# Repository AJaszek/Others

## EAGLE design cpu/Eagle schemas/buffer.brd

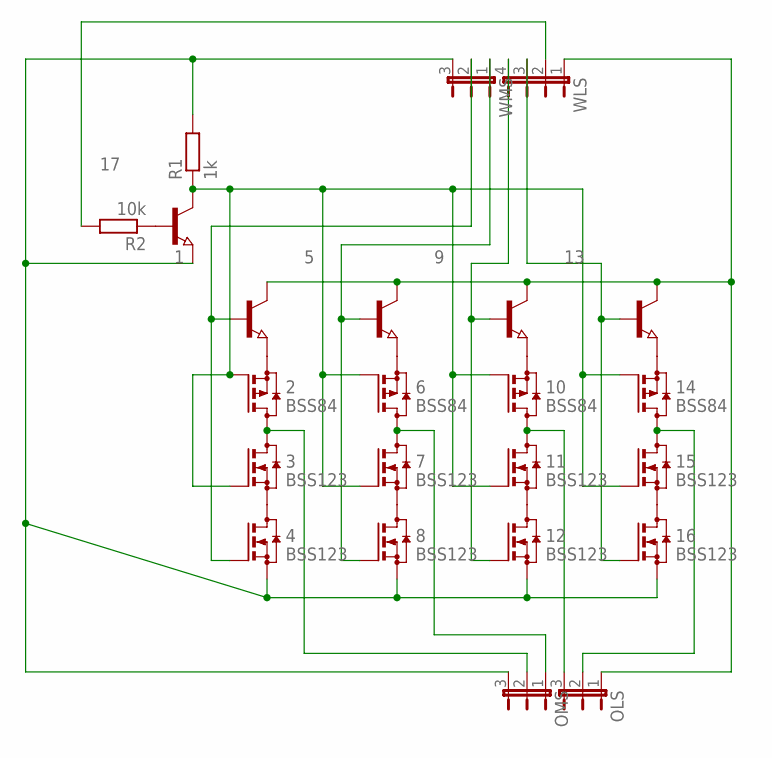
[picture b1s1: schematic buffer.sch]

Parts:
1, 5, 9, 13, 17: NPN-TRANSISTOR_SOT23; SOT23
2, 6, 10, 14: BSS84; SOT23
3, 4, 7, 8, 11, 12, 15, 16: BSS123; SOT23
OLS: JP2E; JP2
OMS: JP2E; JP2
R1: 1k; R1206
R2: 10k; R1206
WLS: JP4E; JP4
WMS: JP2E; JP2

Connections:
unnamed: 13.2 (E), 14.2 (S)
unnamed: 14.3 (D), 15.3 (D), OLS.2
unnamed: 15.2 (S), 16.3 (D)
unnamed: 1.3 (C), 5.3 (C), 9.3 (C), 13.3 (C), OLS.1, WLS.1
unnamed: 13.1 (B), 16.1 (G), WLS.3
unnamed: 4.2 (S), 8.2 (S), 12.2 (S), 16.2 (S), 17.2 (E), OMS.3, R1.2, WMS.3
unnamed: 9.2 (E), 10.2 (S)
unnamed: 10.3 (D), 11.3 (D), OLS.3
unnamed: 11.2 (S), 12.3 (D)
unnamed: 9.1 (B), 12.1 (G), WLS.4
unnamed: 5.2 (E), 6.2 (S)
unnamed: 6.3 (D), 7.3 (D), OMS.1
unnamed: 7.2 (S), 8.3 (D)
unnamed: 5.1 (B), 8.1 (G), WMS.1
unnamed: 1.2 (E), 2.2 (S)
unnamed: 2.3 (D), 3.3 (D), OMS.2
unnamed: 3.2 (S), 4.3 (D)
unnamed: 1.1 (B), 4.1 (G), WMS.2
unnamed: 2.1 (G), 3.1 (G), 6.1 (G), 7.1 (G), 10.1 (G), 11.1 (G), 14.1 (G), 15.1 (G), 17.3 (C), R1.1
unnamed: 17.1 (B), R2.1
unnamed: R2.2, WLS.2

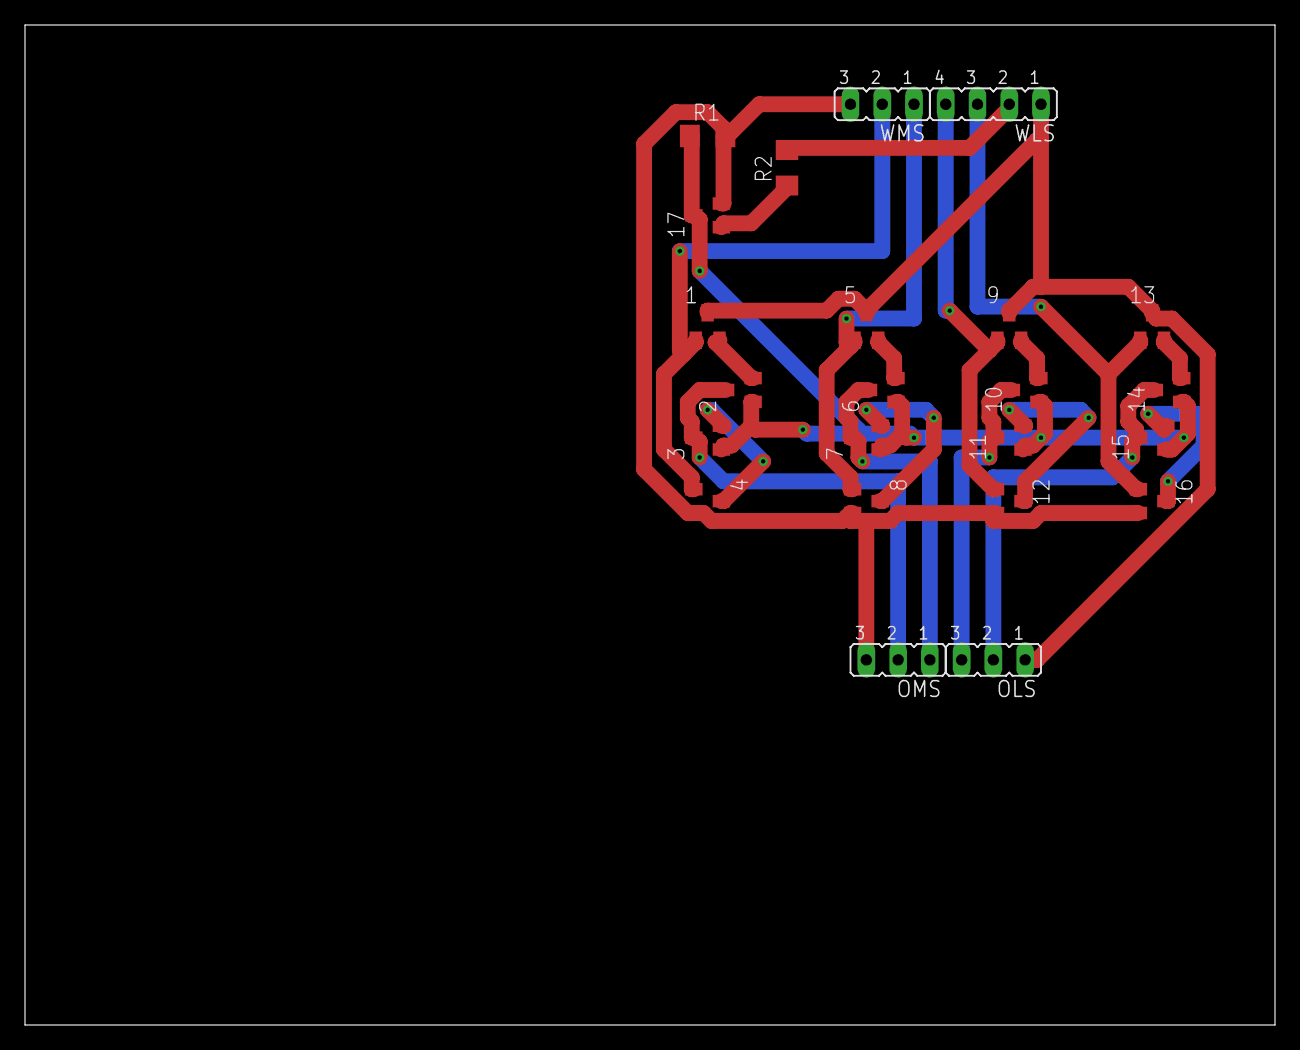
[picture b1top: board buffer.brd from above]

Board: 2 copper layers, 100.0 x 80.0 mm, 23 parts (0 on the bottom side), 21 nets.
